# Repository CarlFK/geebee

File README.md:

# geebee
grabber box - hdmi grabber, camera, microphone ingester composer saver.
streamer too if you want.

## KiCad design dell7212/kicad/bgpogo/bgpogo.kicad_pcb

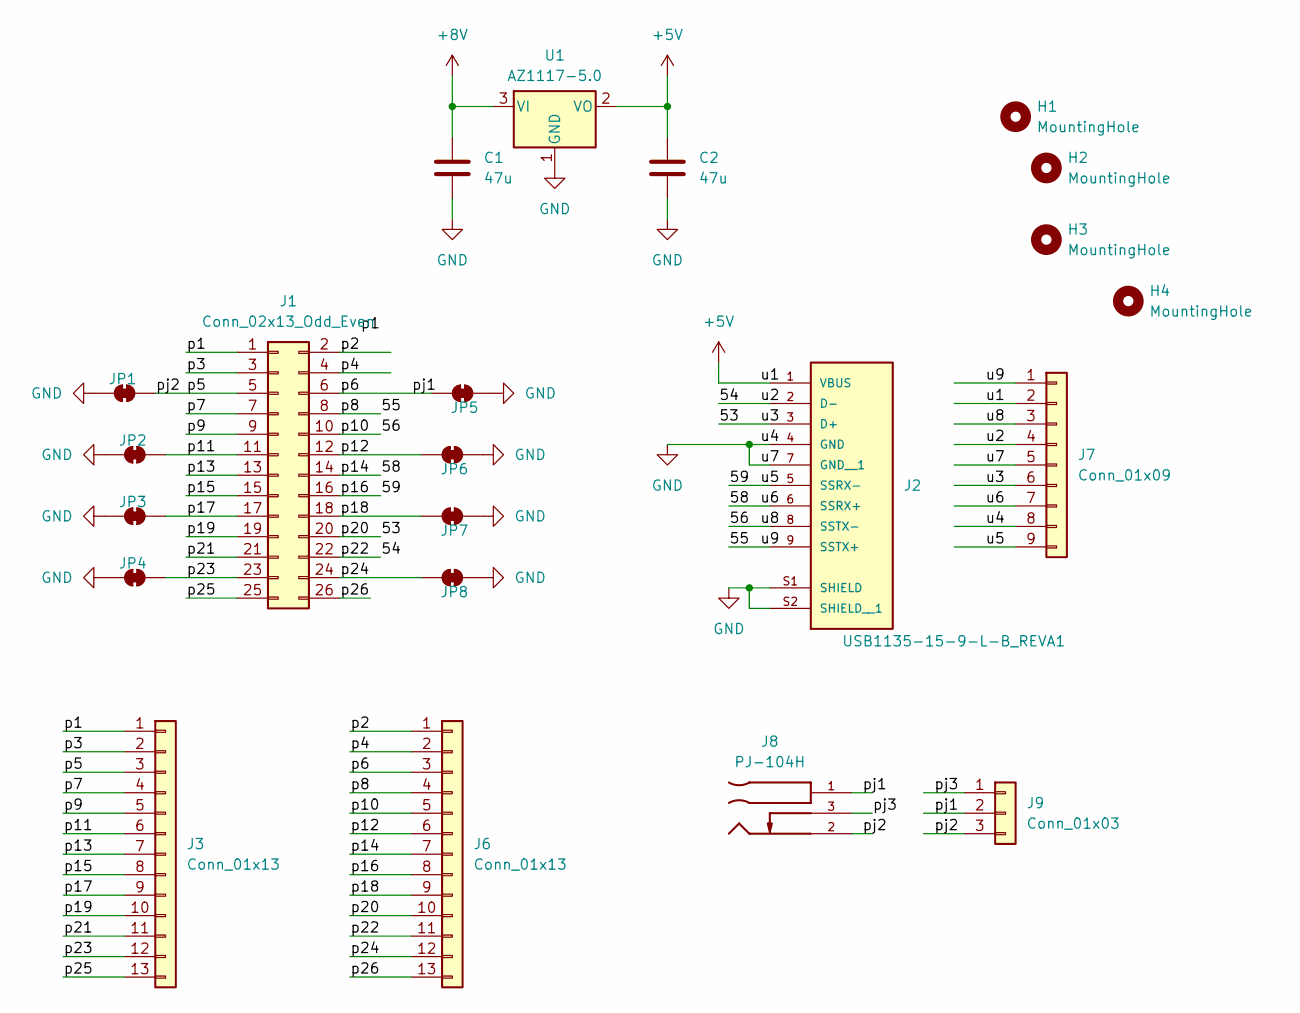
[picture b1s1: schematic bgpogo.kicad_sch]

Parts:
C1, C2: 47u; C_1210_3225Metric_Pad1.33x2.70mm_HandSolder
H1, H2, H3, H4: MountingHole; MountingHole_2.5mm
J1: Conn_02x13_Odd_Even; dell 72xx pogo
J2: USB1135-15-9-L-B_REVA1; GCT_USB1135-15-9-L-B_REVA1; PARTREV A1
J3, J6: Conn_01x13; PinHeader_1x13_P2.54mm_Vertical
J7: Conn_01x09; PinHeader_1x09_P2.54mm_Vertical
J8: PJ-104H; SAMESKY_PJ-104H; PARTREV 1.0
J9: Conn_01x03; PinHeader_1x03_P2.54mm_Vertical
JP1, JP5: SolderJumper_2_Bridged; SolderJumper-2_P1.3mm_Open_RoundedPad1.0x1.5mm
JP2, JP3, JP4, JP6, JP7, JP8: SolderJumper_2_Bridged; SolderJumper-2_P1.3mm_Bridged_RoundedPad1.0x1.5mm
U1: AZ1117-5.0; TO-252-2

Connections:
+5V: C2.1, J2.1 (VBUS), J7.2, U1.2 (VO)
+8V: C1.1, U1.3 (VI)
/53: J1.20, J2.3 (D+), J6.10, J7.6
/54: J1.22, J2.2 (D-), J6.11, J7.4
/55: J1.8, J2.9 (SSTX+), J6.4, J7.1
/56: J1.10, J2.8 (SSTX-), J6.5, J7.3
/58: J1.14, J2.6 (SSRX+), J6.7, J7.7
/59: J1.16, J2.5 (SSRX-), J6.8, J7.9
/p1: J1.1, J3.1
/p2: J1.2, J6.1
/p3: J1.3, J3.2
/p4: J1.4, J6.2
/p5: J1.5, J3.3, J8.2, J9.3, JP1.2 (B)
/p6: J1.6, J6.3, J8.1, J9.2, JP5.2 (B)
/p7: J1.7, J3.4
/p9: J1.9, J3.5
/p11: J1.11, J3.6, JP2.2 (B)
/p12: J1.12, J6.6, JP6.2 (B)
/p13: J1.13, J3.7
/p15: J1.15, J3.8
/p17: J1.17, J3.9, JP3.2 (B)
/p18: J1.18, J6.9, JP7.2 (B)
/p19: J1.19, J3.10
/p21: J1.21, J3.11
/p23: J1.23, J3.12, JP4.2 (B)
/p24: J1.24, J6.12, JP8.2 (B)
/p25: J1.25, J3.13
/p26: J1.26, J6.13
/pj3: J8.3, J9.1
GND: C1.2, C2.2, J2.4 (GND), J2.7 (GND__1), J2.S1 (SHIELD), J2.S2 (SHIELD__1), J7.5, J7.8, JP1.1 (A), JP2.1 (A), JP3.1 (A), JP4.1 (A), JP5.1 (A), JP6.1 (A), JP7.1 (A), JP8.1 (A), U1.1 (GND)

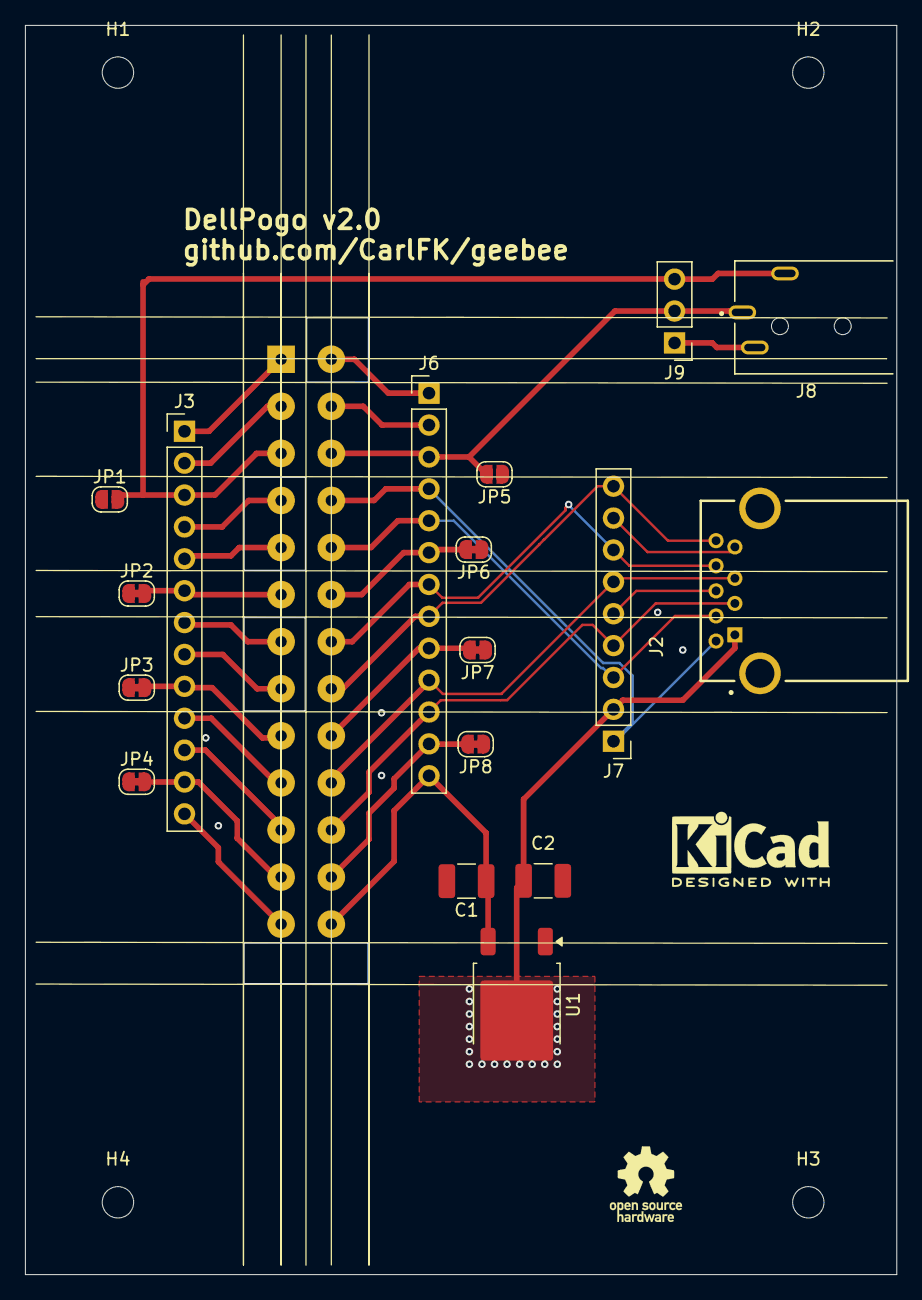
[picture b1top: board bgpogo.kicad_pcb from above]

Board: 2 copper layers, 69.4 x 99.5 mm, 22 parts (0 on the bottom side), 30 nets.

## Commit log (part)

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2025-02-18 all the things. blocker issues coming soon.
2025-02-20 udev and systemd almost working
2025-05-01 py are py not sh templates
2025-05-01 all the rest
2025-05-26 scope creep.
2025-05-26 clean up videoteam-ingest.service
2025-05-26 rename orangepiultrasometing to opi
2025-05-26 check in my inventory
2025-05-26 trim down voctocore-cmds, prep for cmd.txt file.
2025-05-26 remove unused recordings-playback script.
2025-05-26 organize templates into etc and systemd dirs.
2025-05-26 document startup sequence.
2025-05-26 add local-monitor to show presenter hdmi/camera.
2025-05-26 Add local-monitor.sh to systemd.
2025-05-26 more orgainzing source files into systemd and etc dirs.
2025-05-26 add foo-all-the-things scripts
2025-05-26 oPi camera
2025-05-28 no hardcoded things in all-the-things.
2025-05-28 no wayland on Orange I guess.
2025-05-28 sort usb device names.
2025-05-28 enable the .path systemd
2025-05-28 something needs gstreamer1.0-libav. encode and save maybe.
2025-05-28 document systemd tree
2025-05-28 oPi IPs
2025-05-28 Trying the new gst encode/save to disk.
2025-05-28 move voctocore-cmds to its own systemd script. which isn't working, yet.
2025-05-29 No password needed for sudo.
2025-05-30 v-cmds enable and daemon_reexec.
2025-05-30 less fancy systemd dependencies.
2025-05-30 new opi IP
2025-06-01 voctomix systemd harmony.
2025-06-01 test out, real in.
2025-06-01 OrangePi setup
2025-06-01 apt voctomix-outcasts so the binary can be stepped on.
2025-06-01 disable docker from oPi Debian image.
2025-06-06 add sidedoor.
2025-06-06 sidedoor inventory
2025-06-07 ansible pass, but videoteam-ingest-0.path disabled :(
2025-06-07 move enabled: true to Enable task. add test_voc tag.
2025-06-07 fix typo: dispay.
2025-06-08 Don't reload/reexec when enableing systemds?
2025-06-08 ansible oPi via sidedoor
2025-06-08 clean up ansit.sh.
2025-06-14 xfce autologin.
2025-06-14 Install xfce on _server base.
2025-06-14 remove all the docker things.
2025-06-14 apt autoclean autoremove
2025-06-15 install 7z to un-7 opi image.7z
2025-06-19 Add some random packages to install for R&D.
2025-09-01 now on Dell 7212
2025-09-27 git fix
2025-09-27 random notes. should be on the wiki.
2025-09-27 fix kernel.deb url
2025-09-27 consistant formatting.
2025-09-27 put Orange Pi things into one role
2025-09-28 opi and dell72xx isolated.
2025-09-30 DISPLAY=:0
2025-10-01 forky sources for trixie.
2025-10-01 everrything I need working 16.7 kernel
2025-10-05 kernel-oct5 conf and deb
2025-10-12 reorg soures/ingest/sinks.
2025-10-21 kicad sch
2025-10-22 pogo sch maybe ready
2025-10-22 pogo sch assign header footprints.
2025-10-22 more nets.
2025-10-22 board v01
2025-10-22 board v.9
2025-10-22 board v1.0 ordered
2026-01-09 unground the groungs
2026-01-09 route the not-groungs, but small trace width
2026-01-09 ground plane, gnd not connected (bad).
2026-01-09 ground pogos connected to GND via solder bridge. and bigger traces.
2026-01-10 power nets, not really.
2026-01-10 Power Now.
2026-01-10 pogo alignment lines.
2026-01-10 holes to help align the pogos with pads.
2026-01-10 spam
2026-01-12 better power plug lables and header placement.
2026-01-12 ref image for back pack pogo mounting holes
2026-01-12 better alignment lines and holes. lots of DRC violations.
2026-03-12 d-i late command
2026-03-19 OIDIA
2026-03-19 voc-vocto
2026-03-19 no firmware-nonfree, just firmware-intel-graphics
2026-03-22 Script-ish to install voctomix dev dependencies.
2026-03-22 set grub to 640x480
2026-03-22 rearange voctodev_deps apt
2026-03-23 add magic audio.original=0+1
2026-03-23 more vocto dev deps
2026-04-11 netplan wifi
2026-04-11 use carlfk/gst voctomix
2026-04-11 tag ini for core.ini
2026-04-11 audio.original=0+1 to only the last source
2026-04-11 tag wifi
2026-04-15 support for mulitiple wifi ssid/pw.
2026-04-15 install the font we need and a bunch of others because I don't know what package has the font we need.
2026-04-15 touch up sidedoor readme.
2026-04-15 Update README.md ssh-keyscan
2026-04-17 much commits.
2026-04-17 more cam debug
2026-04-17 pointers to the debconf ansible that I make use of.
2026-04-17 use ssh-import-id to add keys.
2026-04-18 Dell 7202 boxs
2026-04-19 install kernel 6.19 from -backports.
2026-04-23 mipi/usb camera split
2026-04-23 commands to make vocoto core dance so we know some things are working.
2026-04-23 only install linux from forky for mipi cams.
2026-04-23 take sparkle out of test group.
2026-04-23 forky kernel for mipi cam.
2026-04-23 use ccc vocto systemd service files.
2026-04-23 define forky_kernel: false for all (turn on for mipi.)
2026-04-23 add KiCad artifact files to .gitignore
2026-04-23 usb cam works, voc systemd works, cmds work.
2026-04-23 inventory driven extra packages
2026-04-23 tag sugar apt
2026-04-23 quote {{}}
2026-04-27 add DC recording_format to videoteam-record.service.
2026-04-27 unsuccessful floundering with systemd core-cmd triggering.
2026-04-27 migrate ccc core,sink service to dc names.
2026-04-27 add ansible --tags init,systemd
2026-05-01 install vivid everywhere.
2026-05-01 pipewire-bin to appease pw.conf: can't load config client.conf: No such file or directory.
2026-05-01 more wifi everywhere
2026-05-01 cam and vivid as default video sources.
2026-05-01 add lec_43 to vocto.cmds
2026-05-01 more systemd fail.
2026-05-01 source.kind so I can turn off gst and use test.
2026-05-01 shuffle inventory groups
2026-05-02 #comment out unneeded vocto commands to make logs less messy.
2026-05-02 systemd status: good enough. let core faf while cmds --wait-for-core.
2026-05-09 set blue room.
2026-05-10 script to merge PRs into main
2026-05-10 more systemd floundering.
2026-05-10 try to make core wait for DE to be up and ready.
2026-05-10 full filenames, not clever hard to understand conventions.
2026-05-12 gbtest.yml to make a generic geebee box.
2026-05-12 add gbtest to inventory
2026-05-12 appease git merge Committer identity unknown
2026-05-12 remove git_merge debugging logging.
2026-05-13 default sources: gst ball and vivi
2026-05-13 shuffle and reformat inventory
2026-05-13 add ExecStartPres to gbtest to make core wait for windows and audio systems to be up enough for core to start and monitor.
2026-05-13 more v's to cores -v
2026-05-15 use CarlFK bugfix/falbacksrc
2026-05-15 don't rely on audio hardware for gbtest.
2026-05-15 remove duplicate default ingest_sources.
2026-05-15 more removing audio device from gbtest.
2026-05-15 add console=tty0 to gbtest
2026-05-15 use ccc vocto main.
2026-05-15 move grub settings from fix-dell to its own role.
2026-05-17 move grub parameters to grub role.
2026-05-17 forky_kernel is for mipi cam.
2026-05-17 avenc_ac3 to save 6 audio channels.
2026-06-03 install gstreamer1.0-plugins-base-apps for gst-discoverer
2026-06-03 systemd starts gui.
2026-06-04 script to post conf files to ndv public site.
2026-06-06 add sidedoor command to motd.
2026-06-11 enable av hardware for d7212 group.
2026-06-11 cutlist systemd
2026-06-14 prometheus dep.
